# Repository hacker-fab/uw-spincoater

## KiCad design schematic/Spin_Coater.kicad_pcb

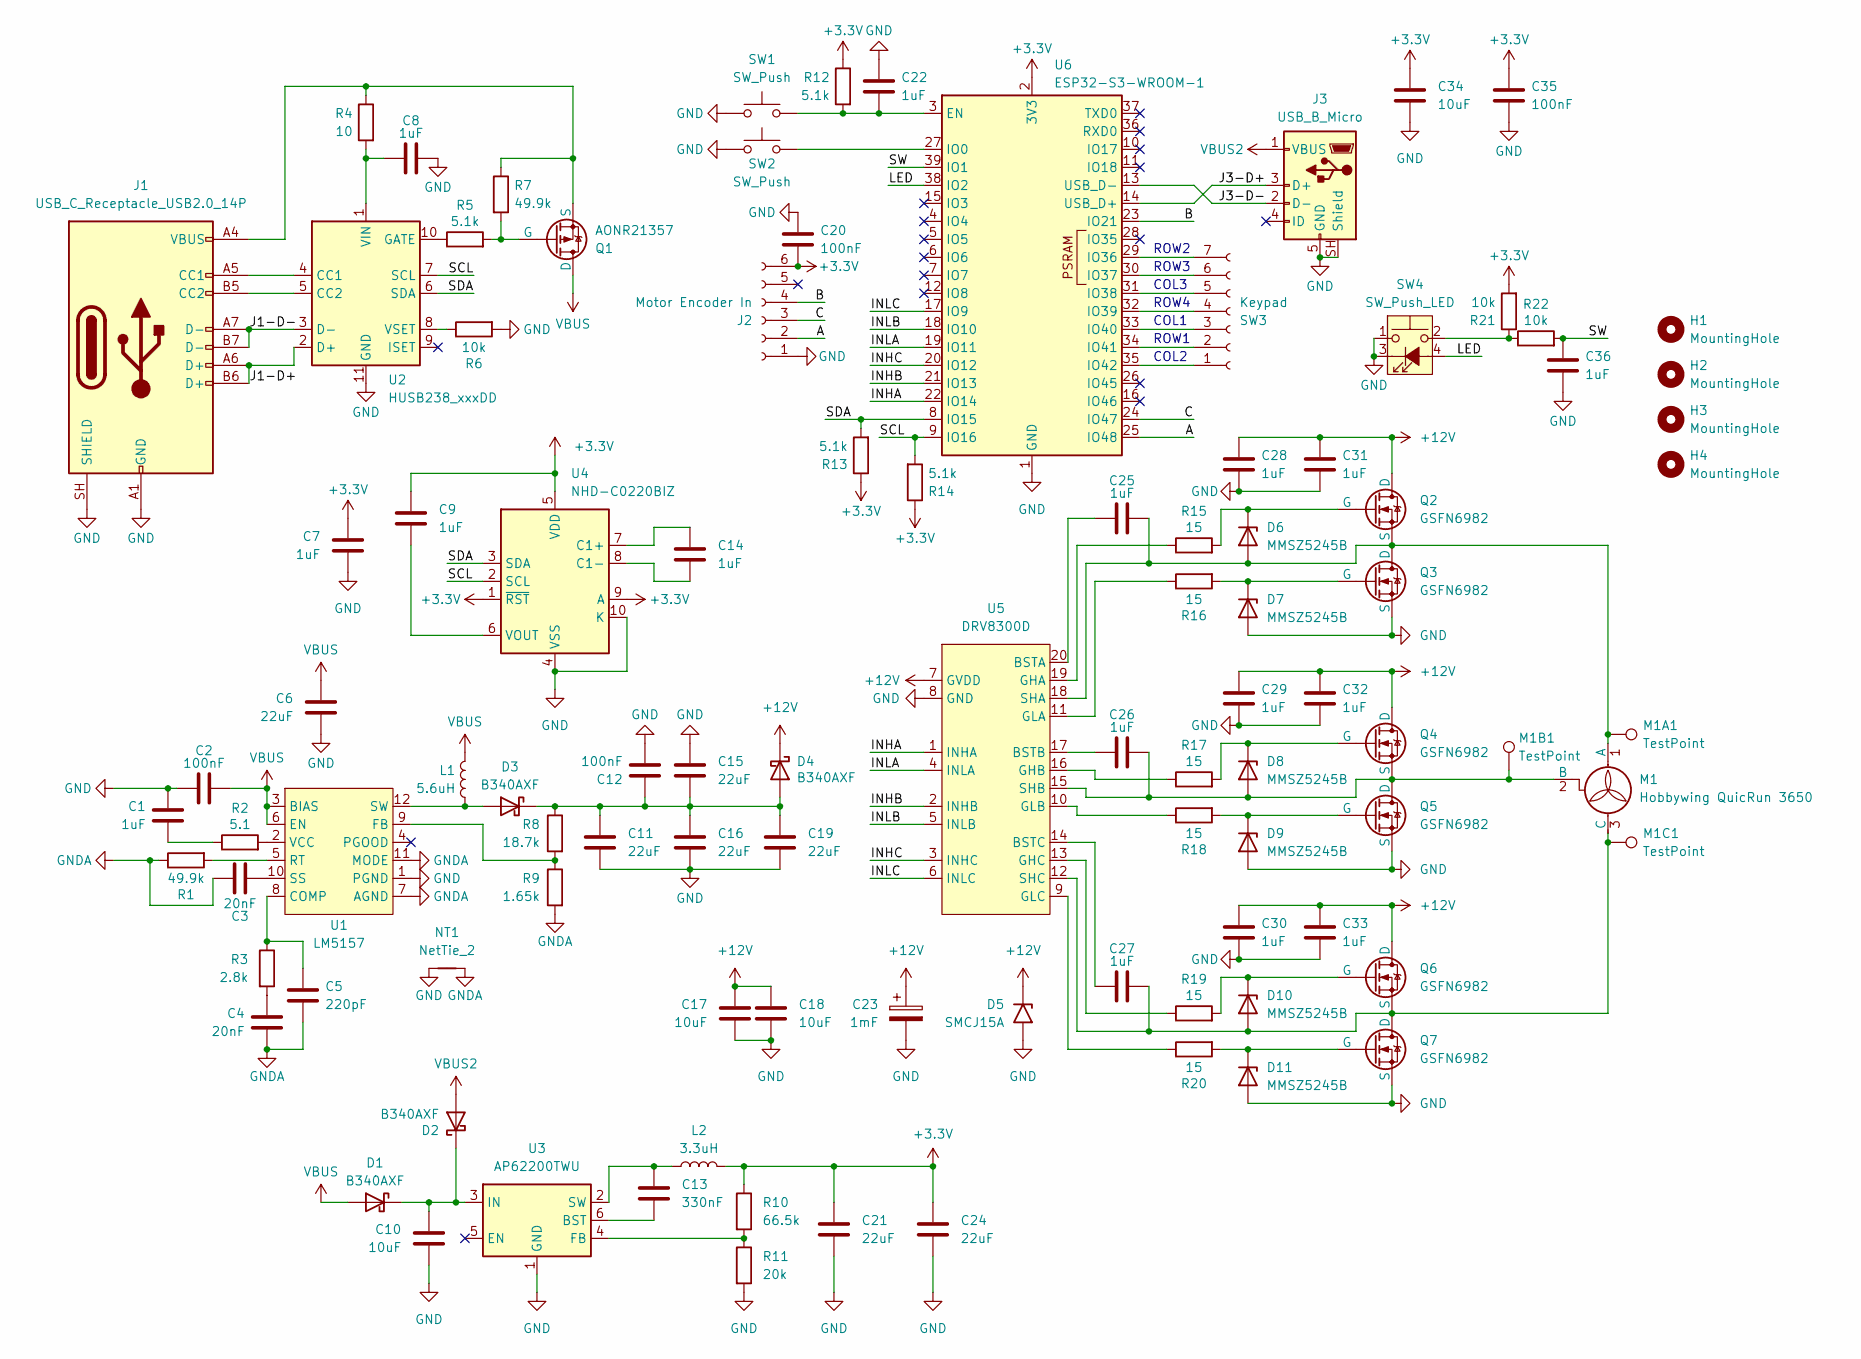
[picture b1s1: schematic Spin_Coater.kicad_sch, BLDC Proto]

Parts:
C1, C7, C8, C9, C14, C22, C25, C26, C27, C28, C29, C30, C31, C32, C33, C36: 1uF; C_0805_2012Metric
C2, C12, C20, C35: 100nF; C_0805_2012Metric
C3, C4: 20nF; C_0805_2012Metric
C5: 220pF; C_0805_2012Metric
C6, C11, C15, C16, C19, C21, C24: 22uF; C_1210_3225Metric
C10, C17, C18, C34: 10uF; C_1206_3216Metric
C13: 330nF; C_0805_2012Metric
C23: 1mF; CP_Radial_D13.0mm_P5.00mm
D1, D2, D3, D4: B340AXF; D_SMA
D5: SMCJ15A; D_SMC
D6, D7, D8, D9, D10, D11: MMSZ5245B; D_SOD-123
H1, H2, H3, H4: MountingHole; MountingHole_3.2mm_M3
J1: USB_C_Receptacle_USB2.0_14P; UJ20-C-H-G-SMT-2A-P16-TR
J2: Motor Encoder In; JST_ZH_B6B-ZR_1x06_P1.50mm_Vertical
J3: USB_B_Micro; UJ2-MIBH-G-SMT-TR
L1: 5.6uH; HPAL1V0630
L2: 3.3uH; HPC5040NF
M1: Hobbywing QuicRun 3650
M1A1, M1B1, M1C1: TestPoint; TestPoint_THTPad_D5.5mm_Drill3.5mm
NT1: NetTie_2; NetTie-2_SMD_Pad0.25mm
Q1: AONR21357; PPAK3x3
Q2, Q3, Q4, Q5, Q6, Q7: GSFN6982; PPAK3x3
R1, R7: 49.9k; R_0805_2012Metric
R2: 5.1; R_0805_2012Metric
R3: 2.8k; R_0805_2012Metric
R4: 10; R_0805_2012Metric
R5, R12, R13, R14: 5.1k; R_0805_2012Metric
R6, R21, R22: 10k; R_0805_2012Metric
R8: 18.7k; R_0805_2012Metric
R9: 1.65k; R_0805_2012Metric
R10: 66.5k; R_0805_2012Metric
R11: 20k; R_0805_2012Metric
R15, R16, R17, R18, R19, R20: 15; R_0805_2012Metric
SW1, SW2: SW_Push; SW_PUSH_6mm
SW3: Keypad; PinHeader_1x07_P2.54mm_Vertical
SW4: SW_Push_LED; PinSocket_2x02_P2.54mm_Vertical
U1: LM5157; WQFN-16-1EP_3x3mm_P0.5mm_EP1.68x1.68mm_ThermalVias
U2: HUSB238_xxxDD; WDFN-10-1EP_3x3mm_P0.5mm_EP1.8x2.5mm
U3: AP62200TWU; TSOT-23-6
U4: NHD-C0220BIZ; NHD-C0220BiZ
U5: DRV8300D; TSSOP-20_4.4x6.5mm_P0.65mm
U6: ESP32-S3-WROOM-1

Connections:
+3.3V: C7.1, C9.1, C20.2, C21.1, C24.1, C34.1, C35.1, J2.6, L2.2, R10.1, R12.1, R13.1, R14.1, R21.2, U4.1 (~RST), U4.5 (VDD), U4.9 (A), U6.2 (3V3)
+12V: C17.1, C18.1, C23.1, C28.1, C29.1, C30.1, C31.1, C32.1, C33.1, D4.1 (K), D5.1 (A1), Q2.5 (D), Q4.5 (D), Q6.5 (D), U5.7 (GVDD)
/A: J2.2, U6.25 (IO48)
/B: J2.4, U6.23 (IO21)
/C: J2.3, U6.24 (IO47)
/INHA: U5.1 (INHA), U6.22 (IO14)
/INHB: U5.2 (INHB), U6.21 (IO13)
/INHC: U5.3 (INHC), U6.20 (IO12)
/INLA: U5.4 (INLA), U6.19 (IO11)
/INLB: U5.5 (INLB), U6.18 (IO10)
/INLC: U5.6 (INLC), U6.17 (IO9)
/J1-D+: J1.A6 (D+), J1.B6 (D+), U2.2 (D+)
/J1-D-: J1.A7 (D-), J1.B7 (D-), U2.3 (D-)
/J3-D+: J3.3 (D+), U6.14 (USB_D+)
/J3-D-: J3.2 (D-), U6.13 (USB_D-)
/LED: SW4.4 (A), U6.38 (IO2)
/SCL: R14.2, U2.7 (SCL), U4.2 (SCL), U6.9 (IO16)
/SDA: R13.2, U2.6 (SDA), U4.3 (SDA), U6.8 (IO15)
/SW: C36.1, R22.2, U6.39 (IO1)
GND: C1.1, C2.1, C6.2, C7.2, C8.2, C10.2, C11.2, C12.2, C15.1, C16.2, C17.2, C18.2, C19.2, C20.1, C21.2, C22.1, C23.2, C24.2, C28.2, C29.2, C30.2, C31.2, C32.2, C33.2, C34.2, C35.2, C36.2, D5.2 (A2), D7.2 (A), D9.2 (A), D11.2 (A), J1.A1 (GND), J1.A12 (GND), J1.B1 (GND), J1.B12 (GND), J1.SH (SHIELD), J2.1, J3.5 (GND), J3.SH (Shield), NT1.1, Q3.1 (S), Q3.2 (S), Q3.3 (S), Q5.1 (S), Q5.2 (S), Q5.3 (S), Q7.1 (S), Q7.2 (S), Q7.3 (S), R6.2, R11.2, SW1.1, SW2.1, SW4.1, SW4.3 (K), U1.1 (PGND), U1.16 (PGND), U1.17 (PGND), U2.11 (GND), U3.1 (GND), U4.4 (VSS), U4.10 (K), U5.8 (GND), U6.1 (GND), U6.40 (GND), U6.41 (GND)
GNDA: C3.1, C4.2, C5.2, NT1.2, R1.1, R9.2, U1.7 (AGND), U1.11 (MODE)
unnamed: C1.2, R2.1
unnamed: C4.1, R3.2
unnamed: C10.1, D1.1 (K), D2.1 (K), U3.3 (IN)
unnamed: D3.2 (A), L1.2, U1.12 (SW), U1.13 (SW), U1.14 (SW)
unnamed: C11.1, C12.1, C15.2, C16.1, C19.1, D3.1 (K), D4.2 (A), R8.1
unnamed: C25.2, D6.2 (A), M1.1 (A), M1A1.1 (1_1), Q2.1 (S), Q2.2 (S), Q2.3 (S), Q3.5 (D), U5.18 (SHA)
unnamed: D6.1 (K), Q2.4 (G), R15.2
unnamed: D7.1 (K), Q3.4 (G), R16.2
unnamed: C26.2, D8.2 (A), M1.2 (B), M1B1.1 (1_1), Q4.1 (S), Q4.2 (S), Q4.3 (S), Q5.5 (D), U5.15 (SHB)
unnamed: D8.1 (K), Q4.4 (G), R17.2
unnamed: D9.1 (K), Q5.4 (G), R18.2
unnamed: C27.2, D10.2 (A), M1.3 (C), M1C1.1 (1_1), Q6.1 (S), Q6.2 (S), Q6.3 (S), Q7.5 (D), U5.12 (SHC)
unnamed: D10.1 (K), Q6.4 (G), R19.2
unnamed: D11.1 (K), Q7.4 (G), R20.2
unnamed: J1.A5 (CC1), U2.4 (CC1)
unnamed: J1.B5 (CC2), U2.5 (CC2)
unnamed: J1.A4 (VBUS), J1.A9 (VBUS), J1.B4 (VBUS), J1.B9 (VBUS), Q1.1 (S), Q1.2 (S), Q1.3 (S), R4.1, R7.1
unnamed: Q1.4 (G), R5.2, R7.2
unnamed: R21.1, R22.1, SW4.2
unnamed: SW3.1, U6.35 (IO42)
unnamed: SW3.2, U6.34 (IO41)
unnamed: SW3.3, U6.33 (IO40)
unnamed: SW3.4, U6.32 (IO39)
unnamed: SW3.5, U6.31 (IO38)
unnamed: SW3.6, U6.30 (IO37)
unnamed: SW3.7, U6.29 (IO36)
unnamed: C5.1, R3.1, U1.8 (COMP)
unnamed: R8.2, R9.1, U1.9 (FB)
unnamed: R1.2, U1.5 (RT)
unnamed: C3.2, U1.10 (SS)
unnamed: R2.2, U1.2 (VCC)
unnamed: R5.1, U2.10 (GATE)
unnamed: C8.1, R4.2, U2.1 (VIN)
unnamed: R6.1, U2.8 (VSET)
unnamed: C13.2, U3.6 (BST)
unnamed: R10.2, R11.1, U3.4 (FB)
unnamed: C13.1, L2.1, U3.2 (SW)
unnamed: C14.1, U4.7 (C1+)
unnamed: C14.2, U4.8 (C1-)
unnamed: C9.2, U4.6 (VOUT)
unnamed: C25.1, U5.20 (BSTA)
unnamed: C26.1, U5.17 (BSTB)
unnamed: C27.1, U5.14 (BSTC)
unnamed: R15.1, U5.19 (GHA)
unnamed: R17.1, U5.16 (GHB)
unnamed: R19.1, U5.13 (GHC)
unnamed: R16.1, U5.11 (GLA)
unnamed: R18.1, U5.10 (GLB)
unnamed: R20.1, U5.9 (GLC)
unnamed: C22.2, R12.2, SW1.2, U6.3 (EN)
unnamed: SW2.2, U6.27 (IO0)
VBUS: C2.2, C6.1, D1.2 (A), L1.1, Q1.5 (D), U1.3 (BIAS), U1.6 (EN)
VBUS2: D2.2 (A), J3.1 (VBUS)

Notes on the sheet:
ROW2
COL2
ROW3
ROW4
COL3
COL1
ROW1

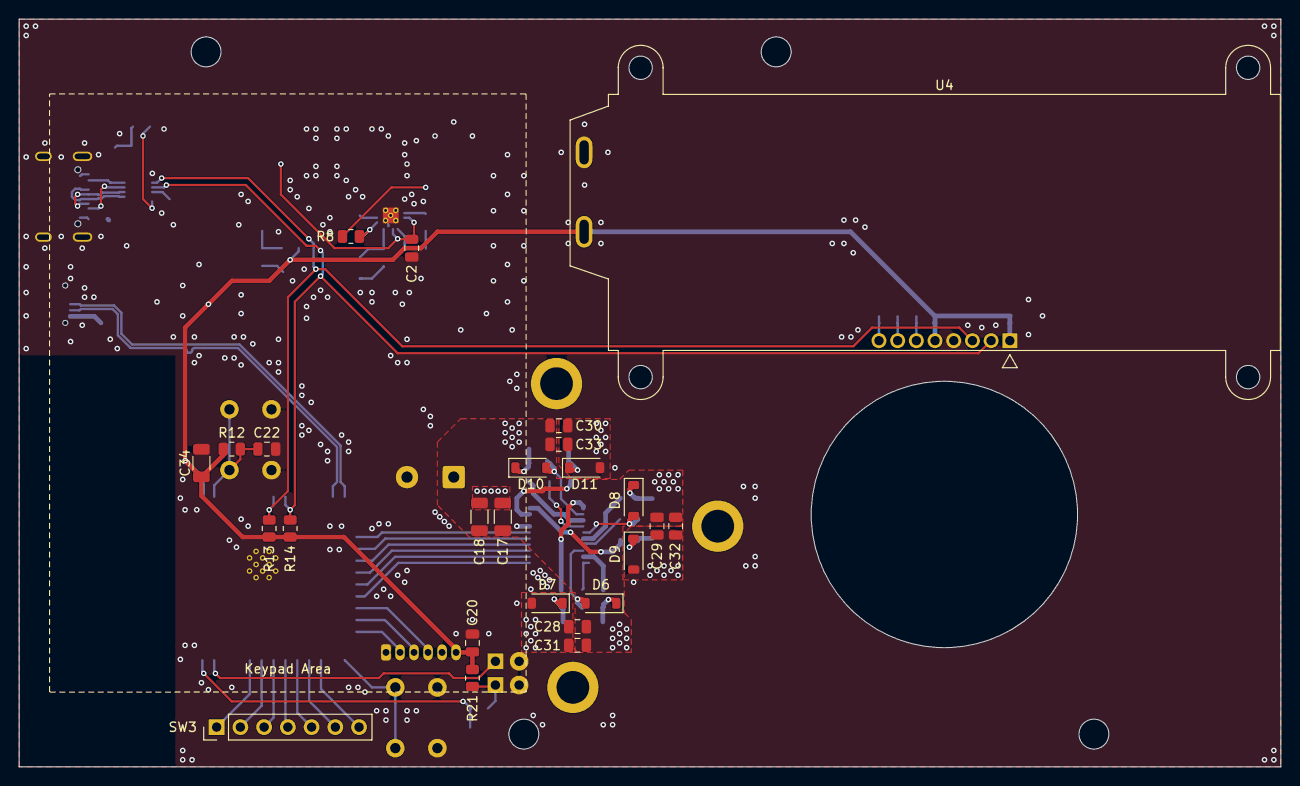
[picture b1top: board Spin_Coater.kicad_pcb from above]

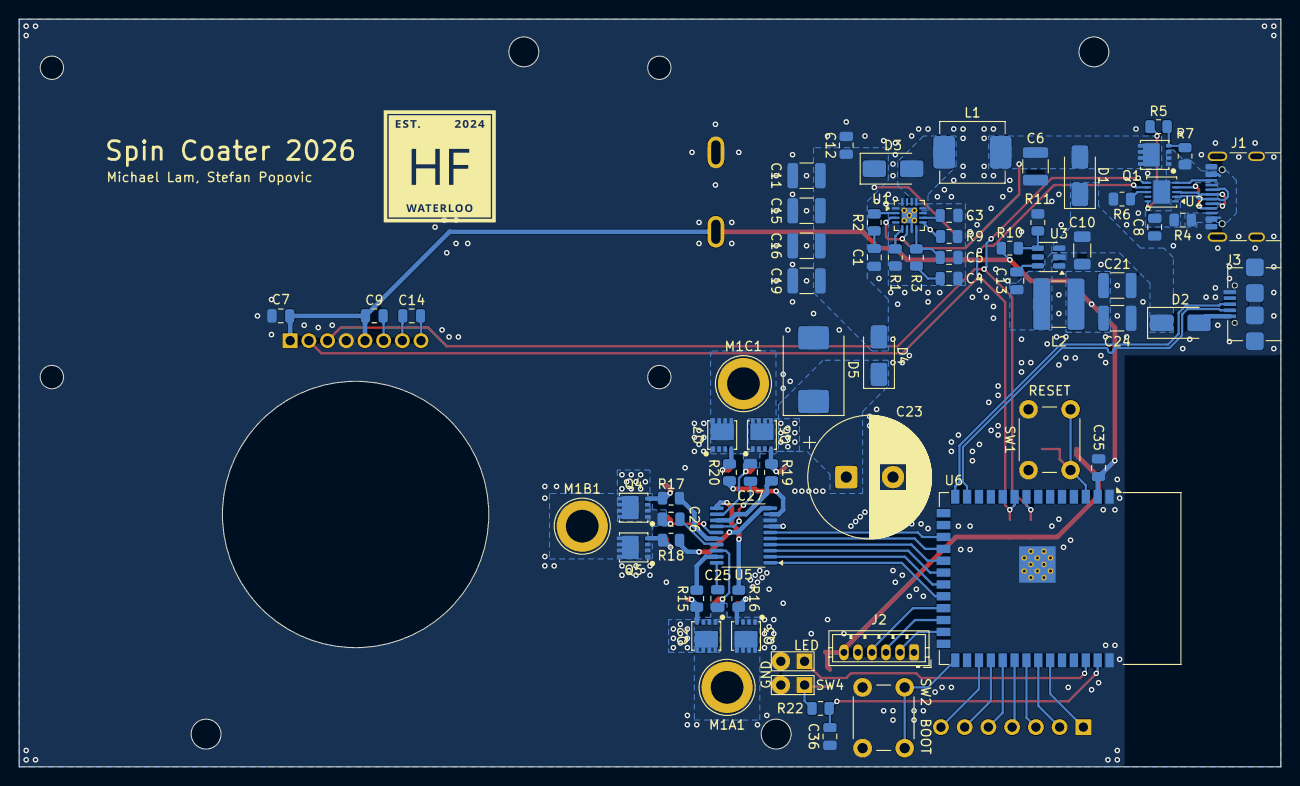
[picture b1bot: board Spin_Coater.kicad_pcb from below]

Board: 2 copper layers, 135.0 x 80.0 mm, 99 parts (70 on the bottom side), 74 nets.

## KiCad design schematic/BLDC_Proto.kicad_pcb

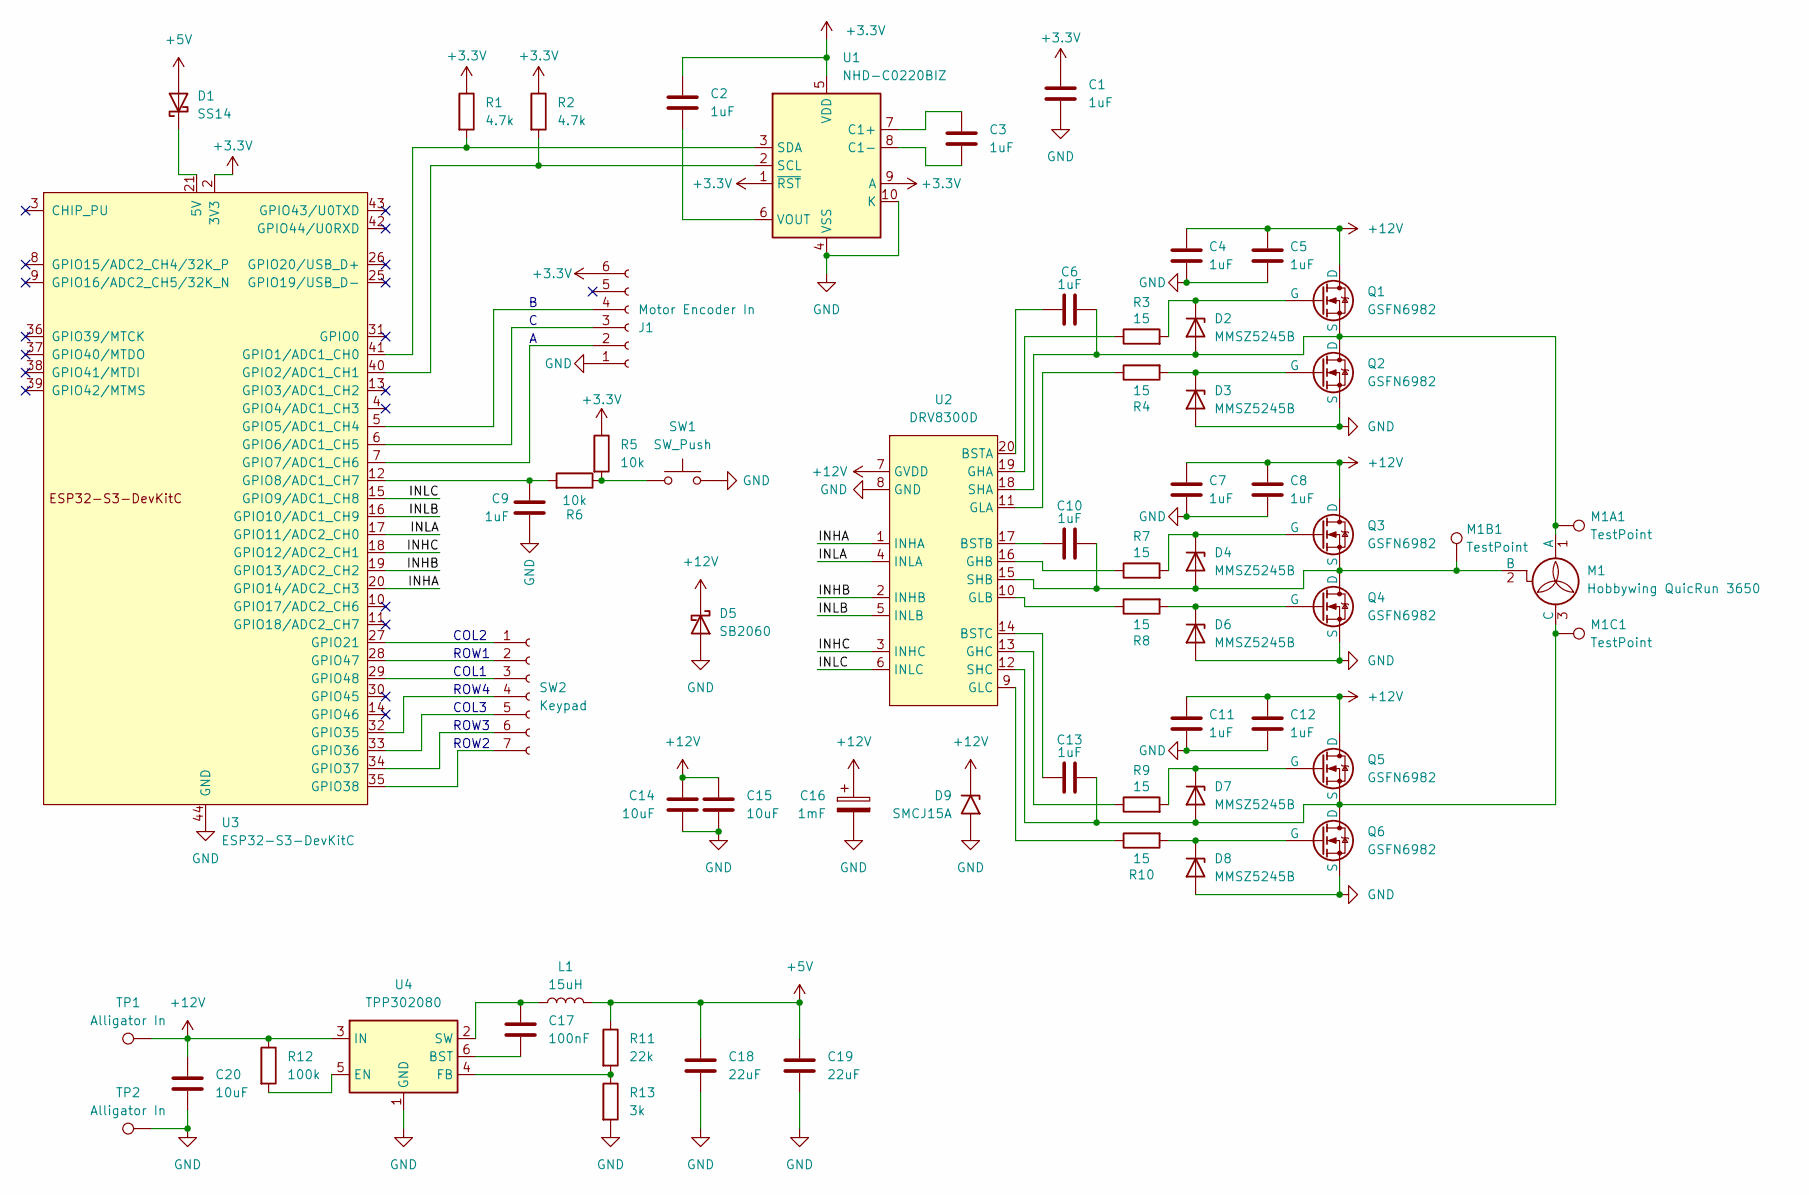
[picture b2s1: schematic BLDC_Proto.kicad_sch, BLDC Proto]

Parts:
C1, C2, C3, C4, C5, C6, C7, C8, C9, C10, C11, C12, C13: 1uF; C_0805_2012Metric
C14, C15, C20: 10uF; C_1206_3216Metric
C16: 1mF; CP_Radial_D13.0mm_P5.00mm
C17: 100nF; C_0805_2012Metric
C18, C19: 22uF; C_1210_3225Metric
D1: SS14; D_SMA
D2, D3, D4, D6, D7, D8: MMSZ5245B; D_SOD-123
D5: SB2060; D_DO-201AD_P15.24mm_Horizontal
D9: SMCJ15A; D_SMC
J1: Motor Encoder In; JST_ZH_B6B-ZR_1x06_P1.50mm_Vertical
L1: 15uH; HCM1A0805V3-150R
M1: Hobbywing QuicRun 3650
M1A1, M1B1, M1C1: TestPoint; TestPoint_THTPad_D5.0mm_Drill3.0mm
Q1, Q2, Q3, Q4, Q5, Q6: GSFN6982; PPAK3x3
R1, R2: 4.7k; R_0805_2012Metric
R3, R4, R7, R8, R9, R10: 15; R_0805_2012Metric
R5, R6: 10k; R_0805_2012Metric
R11: 22k; R_0805_2012Metric
R12: 100k; R_0805_2012Metric
R13: 3k; R_0805_2012Metric
SW1: SW_Push; SW_PUSH_6mm
SW2: Keypad; PinHeader_1x07_P2.54mm_Vertical
TP1, TP2: Alligator In; 1502-2 Turret
U1: NHD-C0220BIZ; NHD-C0220BiZ
U2: DRV8300D; TSSOP-20_4.4x6.5mm_P0.65mm
U3: ESP32-S3-DevKitC
U4: TPP302080; TSOT-23-6

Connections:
+3.3V: C1.1, C2.1, J1.6, R1.1, R2.1, R5.1, U1.1 (~RST), U1.5 (VDD), U1.9 (A), U3.1 (3V3), U3.2 (3V3)
+5V: C18.1, C19.1, D1.2 (A), L1.2, R11.1
+12V: C4.1, C5.1, C7.1, C8.1, C11.1, C12.1, C14.1, C15.1, C16.1, C20.1, D5.1 (K), D9.1 (A1), Q1.5 (D), Q3.5 (D), Q5.5 (D), R12.1, TP1.1, U2.7 (GVDD), U4.3 (IN)
/INHA: U2.1 (INHA), U3.20 (GPIO14/ADC2_CH3)
/INHB: U2.2 (INHB), U3.19 (GPIO13/ADC2_CH2)
/INHC: U2.3 (INHC), U3.18 (GPIO12/ADC2_CH1)
/INLA: U2.4 (INLA), U3.17 (GPIO11/ADC2_CH0)
/INLB: U2.5 (INLB), U3.16 (GPIO10/ADC1_CH9)
/INLC: U2.6 (INLC), U3.15 (GPIO9/ADC1_CH8)
GND: C1.2, C4.2, C5.2, C7.2, C8.2, C9.2, C11.2, C12.2, C14.2, C15.2, C16.2, C18.2, C19.2, C20.2, D3.2 (A), D5.2 (A), D6.2 (A), D8.2 (A), D9.2 (A2), J1.1, Q2.1 (S), Q2.2 (S), Q2.3 (S), Q4.1 (S), Q4.2 (S), Q4.3 (S), Q6.1 (S), Q6.2 (S), Q6.3 (S), R13.2, SW1.2, TP2.1, U1.4 (VSS), U1.10 (K), U2.8 (GND), U3.22 (GND), U3.23 (GND), U3.24 (GND), U3.44 (GND), U4.1 (GND)
unnamed: D1.1 (K), U3.21 (5V)
unnamed 11: C6.2, D2.2 (A), M1.1 (A), M1A1.1, Q1.1 (S), Q1.2 (S), Q1.3 (S), Q2.5 (D), U2.18 (SHA); also elsewhere on the board
unnamed: D2.1 (K), Q1.4 (G), R3.2
unnamed: D3.1 (K), Q2.4 (G), R4.2
unnamed 14: C10.2, D4.2 (A), M1.2 (B), M1B1.1, Q3.1 (S), Q3.2 (S), Q3.3 (S), Q4.5 (D), U2.15 (SHB); also elsewhere on the board
unnamed: D4.1 (K), Q3.4 (G), R7.2
unnamed: D6.1 (K), Q4.4 (G), R8.2
unnamed 17: C13.2, D7.2 (A), M1.3 (C), M1C1.1, Q5.1 (S), Q5.2 (S), Q5.3 (S), Q6.5 (D), U2.12 (SHC); also elsewhere on the board
unnamed: D7.1 (K), Q5.4 (G), R9.2
unnamed: D8.1 (K), Q6.4 (G), R10.2
unnamed: J1.2, U3.7 (GPIO7/ADC1_CH6)
unnamed: J1.3, U3.6 (GPIO6/ADC1_CH5)
unnamed: J1.4, U3.5 (GPIO5/ADC1_CH4)
unnamed: R5.2, R6.1, SW1.1
unnamed: SW2.1, U3.27 (GPIO21)
unnamed: SW2.2, U3.28 (GPIO47)
unnamed: SW2.3, U3.29 (GPIO48)
unnamed: SW2.4, U3.32 (GPIO35)
unnamed: SW2.5, U3.33 (GPIO36)
unnamed: SW2.6, U3.34 (GPIO37)
unnamed: SW2.7, U3.35 (GPIO38)
unnamed: C3.1, U1.7 (C1+)
unnamed: C3.2, U1.8 (C1-)
unnamed: R2.2, U1.2 (SCL), U3.40 (GPIO2/ADC1_CH1)
unnamed: R1.2, U1.3 (SDA), U3.41 (GPIO1/ADC1_CH0)
unnamed: C2.2, U1.6 (VOUT)
unnamed: C6.1, U2.20 (BSTA)
unnamed: C10.1, U2.17 (BSTB)
unnamed: C13.1, U2.14 (BSTC)
unnamed: R3.1, U2.19 (GHA)
unnamed: R7.1, U2.16 (GHB)
unnamed: R9.1, U2.13 (GHC)
unnamed: R4.1, U2.11 (GLA)
unnamed: R8.1, U2.10 (GLB)
unnamed: R10.1, U2.9 (GLC)
unnamed: C9.1, R6.2, U3.12 (GPIO8/ADC1_CH7)
unnamed: C17.2, U4.6 (BST)
unnamed: R12.2, U4.5 (EN)
unnamed: R11.2, R13.1, U4.4 (FB)
unnamed: C17.1, L1.1, U4.2 (SW)

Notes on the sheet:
ROW2
COL2
ROW3
ROW4
COL3
COL1
ROW1

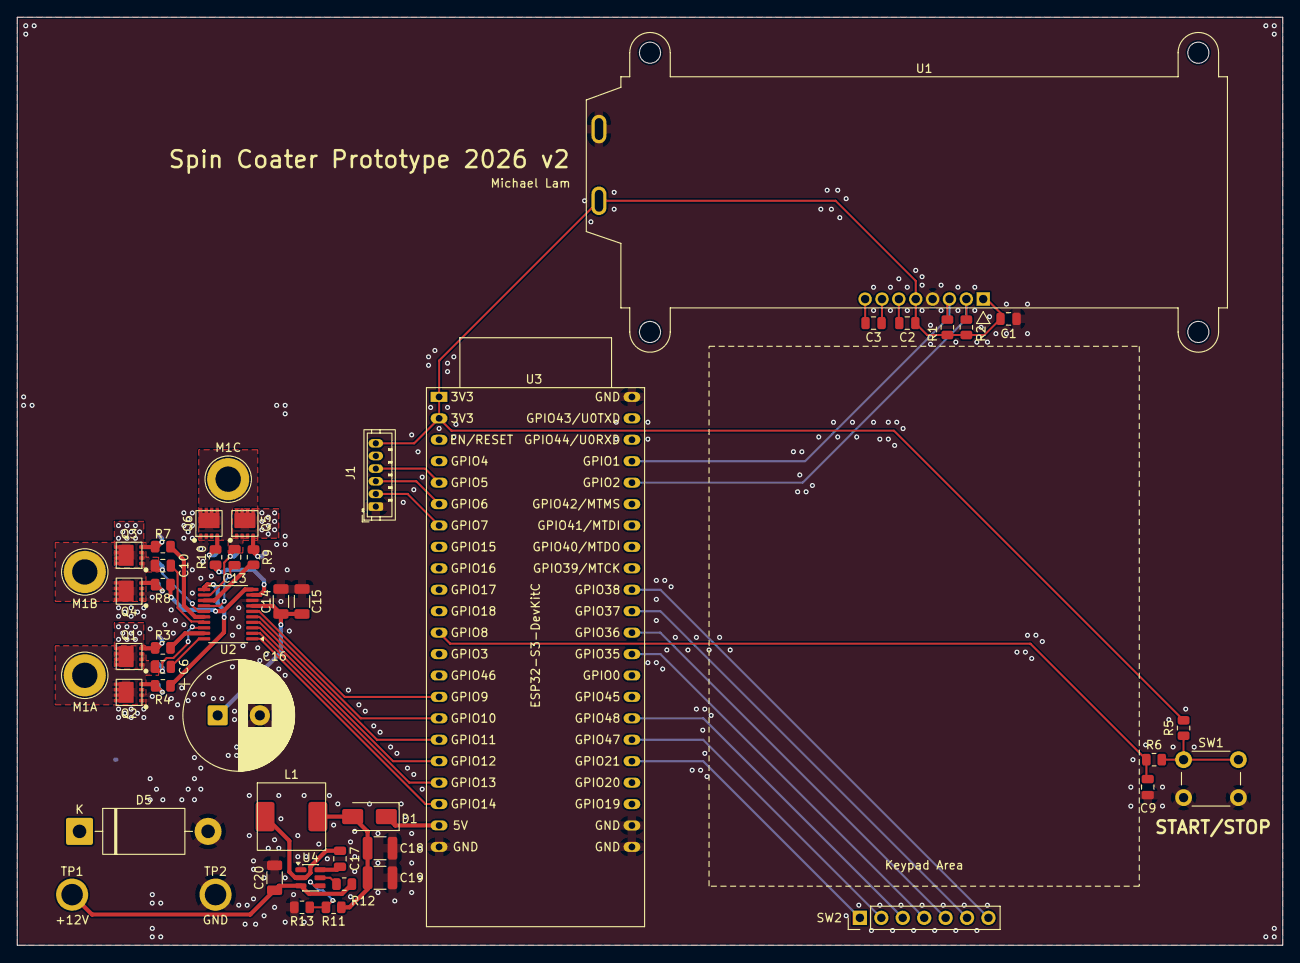
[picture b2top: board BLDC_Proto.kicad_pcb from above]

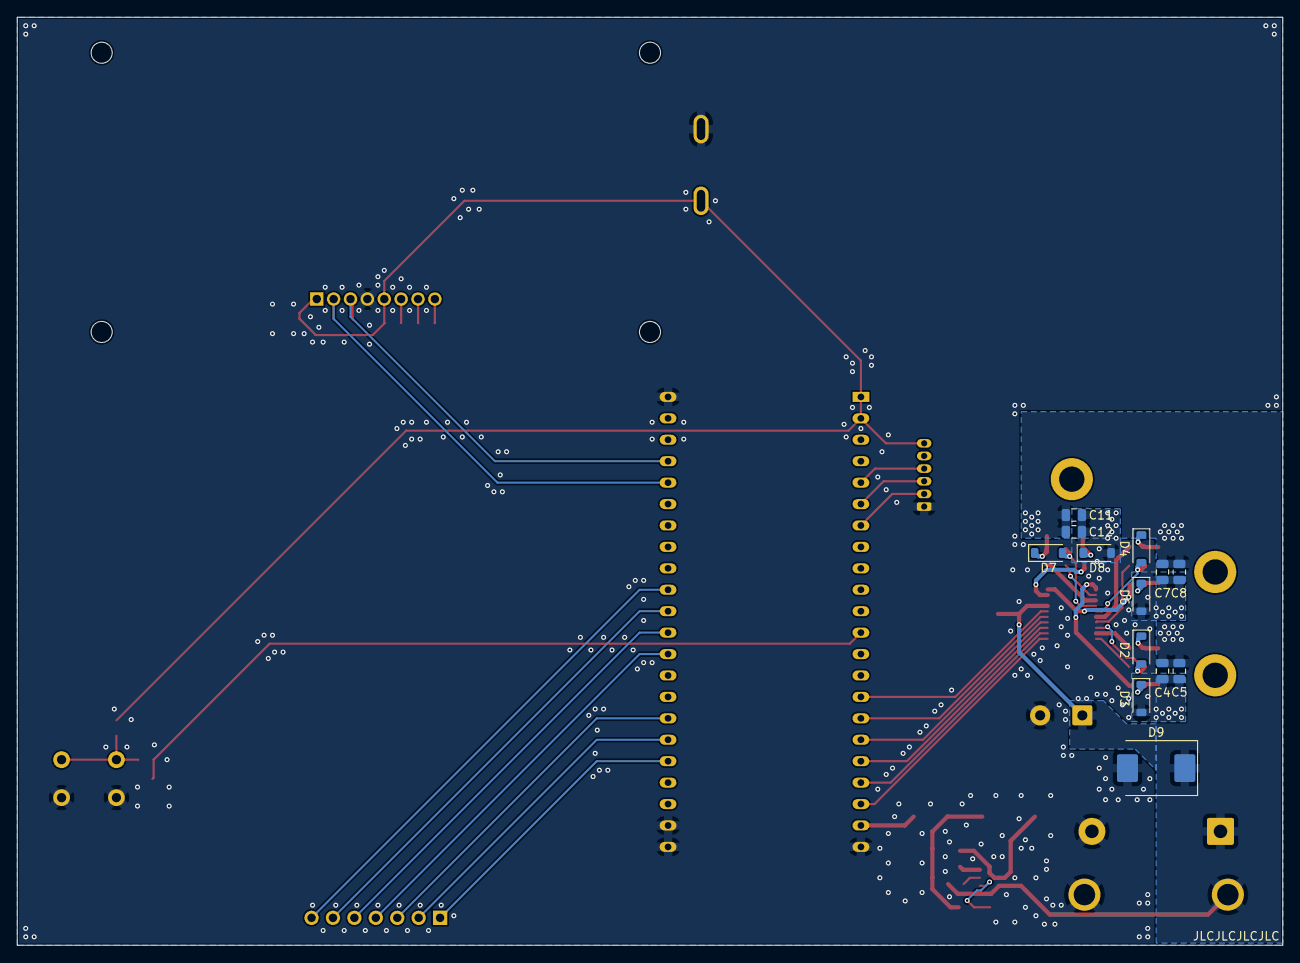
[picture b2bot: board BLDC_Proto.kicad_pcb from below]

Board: 2 copper layers, 150.0 x 110.0 mm, 61 parts (13 on the bottom side), 50 nets.

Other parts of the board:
M1A, M1B, M1C: TestPoint; TestPoint_THTPad_D5.0mm_Drill3.0mm

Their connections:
unnamed 11: M1A.1; also elsewhere on the board
unnamed 14: M1B.1; also elsewhere on the board
unnamed 17: M1C.1; also elsewhere on the board

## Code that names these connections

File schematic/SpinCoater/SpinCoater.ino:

#include <SimpleFOC.h>
#include <Keypad.h>
#include "soft_i2c.h"
#include "async_lcd.h"

#define SDA_PIN 1
#define SCL_PIN 2
#define ENC_A 7
#define ENC_B 5
#define ENC_C 6
#define INHA 14
#define INLA 11
#define INHB 13
#define INLB 10
#define INHC 12
#define INLC 9
#define ROW1 47
#define ROW2 38
#define ROW3 37
#define ROW4 35
#define COL1 48
#define COL2 21
#define COL3 36
#define START_BTN 8

const byte KEYPAD_ROWS = 4;
const byte KEYPAD_COLS = 3;
char keys[KEYPAD_ROWS][KEYPAD_COLS] = {
  {'1','2','3'},
  {'4','5','6'},
  {'7','8','9'},
  {'*','0','#'}
};
byte rowPins[KEYPAD_ROWS] = {ROW1, ROW2, ROW3, ROW4};
byte colPins[KEYPAD_COLS] = {COL1, COL2, COL3};
Keypad keypad = Keypad(makeKeymap(keys), rowPins, colPins, KEYPAD_ROWS, KEYPAD_COLS);

BLDCMotor motor = BLDCMotor(1, 0.112, 2000);  // Assuming delta wiring, tuned to 2000 KV
BLDCDriver6PWM driver = BLDCDriver6PWM(INHA, INLA, INHB, INLB, INHC, INLC);
HallSensor sensor = HallSensor(ENC_A, ENC_B, ENC_C, 1);

SoftI2C  I2CBus(SDA_PIN, SCL_PIN, 100000);
AsyncLCD LCD(I2CBus, 0x3C, 20, 2);

float targetFix = 1.02;
float accelCap = 100; // rads/s^2

volatile float targetVel;
volatile float limitedVel;

volatile int encCount;

unsigned long currTime;
unsigned long tloop;
unsigned long lastTime;
unsigned long lastLCDTick;
unsigned long lastSpeedUpdateTime;
unsigned long lastBtnTime;
unsigned long stoppedBlinkTimer;

bool inputState;
bool stopState;
bool stopped = true;
bool pressed;
int setSpeed;
int tempSetSpeed;

byte plusMinus[] = {0x04, 0x04, 0x1F, 0x04, 0x04, 0x00, 0x1F, 0x00};

void doA(){encCount++; sensor.handleA();}
void doB(){encCount++; sensor.handleB();}
void doC(){encCount++; sensor.handleC();}

void setMotorSpeed(float vel) {
  float outVel = vel; // Another variable in case interrupt happens while constraining
  if (vel < 0) {
    outVel *= -1;
  }
  if (vel < 20 && vel != 0) {
    outVel = 20;
  } else if (vel > 1676) {
    outVel = 1676;
  }
  targetVel = outVel * targetFix;
}

void setup() {
  driver.pwm_frequency = 20000;
  driver.voltage_power_supply = 12;
  driver.init();
  
  sensor.velocity_max = 2000;
  
  sensor.enableInterrupts(doA, doB, doC);
  sensor.init();

  motor.foc_modulation = FOCModulationType::Trapezoid_120;
  motor.torque_controller = TorqueControlType::estimated_current;
  motor.controller = MotionControlType::velocity;
  motor.updateVoltageLimit(12);
  motor.updateCurrentLimit(30); // Arbitrary, does not actually match current

  motor.linkDriver(&driver);
  motor.linkSensor(&sensor);

  motor.zero_electric_angle = 1.047;
  motor.sensor_direction = Direction::CW;

  motor.PID_velocity.P = 0.05;
  motor.PID_velocity.I = 0.4;
  motor.PID_velocity.D = 0;
  motor.LPF_velocity.Tf = 0.0001;
  
  motor.init();
  motor.initFOC();

  I2CBus.begin();
  LCD.begin();
  LCD.createChar(0, plusMinus);
  LCD.setCursor(0, 0);
  LCD.print("Actual:     0");
  LCD.write(0);
  LCD.print("5 RPM");
  LCD.setCursor(0, 1);
  LCD.print("      Stopped");

  pinMode(START_BTN, INPUT);
}

// Max target: 1676 rad/s (~16k RPM), Min target: 20 rad/s (~200 RPM)

void loop() {
  currTime = micros();
  tloop = micros() - lastTime;
  lastTime = currTime;
  float step = accelCap * tloop / 1000000;
  if (limitedVel <= targetVel - step) {
    limitedVel += step;
  } else if (limitedVel >= targetVel + step) {
    limitedVel -= step;
  } else {
    limitedVel = targetVel;
  }
  motor.loopFOC();
  motor.move(limitedVel);

  if (currTime - lastLCDTick >= 100) {
    I2CBus.tick();
    LCD.tick();
    lastLCDTick = micros();
  }
  
  if (currTime - lastBtnTime >= 1000 && !inputState) {
    if (digitalRead(START_BTN)) {
      if (pressed) {
        stopped = !stopped;
        stoppedBlinkTimer = micros();
        stopState = stopped;
        if (stopped) {
          setMotorSpeed(0);
        } else {
          setMotorSpeed(setSpeed * 6.2832 / 60);
        }
        pressed = false;
      }
    } else {
      if (!pressed) {
        pressed = true;
      }
    }
    lastBtnTime = micros();
  }
  
  if (currTime - stoppedBlinkTimer >= 1000000 && !inputState) {
    LCD.setCursor(0, 1);
    if (!stopState) {
      LCD.print(" Set: ");
      LCD.printSpacePaddedInt(setSpeed);
      LCD.write(0);
      LCD.print("1% RPM");
      if (stopped) {
        stopState = true;
      }
    } else if (stopped) {
      LCD.print("      Stopped       ");
      stopState = false;
    }
    stoppedBlinkTimer = micros();
  }
  
  char key = keypad.getKey(); // does not taste better than bread
  if (key) {
      if (key != '*' && key != '#' && !inputState) {
        tempSetSpeed = 0;
        LCD.setCursor(0, 1);
        LCD.print(" Set:     0");
        LCD.write(0);
        LCD.print("1% RPM");
        LCD.setCursor(10, 1);
        LCD.cursor();
        LCD.blink();
        inputState = true;
      }
      if (inputState) {
        if (key == '*') {
          if (tempSetSpeed > 0) {
            tempSetSpeed /= 10;
            LCD.setCursor(6, 1);
            LCD.printSpacePaddedInt(tempSetSpeed);
            LCD.setCursor(10, 1);
          } else {
            LCD.noCursor();
            LCD.noBlink();
            inputState = false;
          }
        } else if (key == '#') {
          if (tempSetSpeed > 16000) {
            tempSetSpeed = 16000;
          }
          if (tempSetSpeed < 200 && tempSetSpeed != 0) {
            tempSetSpeed = 200;
          }
          setSpeed = tempSetSpeed;
          if (!stopped) {
            setMotorSpeed(setSpeed * 6.2832 / 60);
          }
          LCD.noCursor();
          LCD.noBlink();
          inputState = false;
        } else if (tempSetSpeed < 10000) {
          tempSetSpeed = tempSetSpeed * 10 + key - 0x30;
          LCD.setCursor(6, 1);
          LCD.printSpacePaddedInt(tempSetSpeed);
          LCD.setCursor(10, 1);
        }
      }
  }
  
  if (currTime - lastSpeedUpdateTime >= 2000000) {
    LCD.setCursor(8, 0);
    LCD.printSpacePaddedInt(encCount * 5);
    if (inputState) {
      LCD.setCursor(10, 1);
    }
    encCount = 0;
    lastSpeedUpdateTime = micros();
  }
}

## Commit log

2026-02-11 First Revision (DO NOT USE)
2026-02-12 2nd iteration
2026-02-12 Fix typo
2026-02-12 Replace gate driver decoupling capacitor
2026-02-12 Renumber
2026-03-31 Working prototype
2026-05-12 New Version
2026-05-19 Added button debouncing
2026-05-23 Hopefully final revision
2026-05-26 Added timer
2026-05-26 bug fix
